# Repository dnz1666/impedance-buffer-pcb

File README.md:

# Impedance Buffer – PCB Design (RWTH Aachen)

Analog circuit design for a student electric vehicle project (elective module, RWTH Aachen University).

## Circuit Design

- Impedance buffer with low-pass filter
- Non-inverting OpAmp amplifier
- Single-sided PCB layout

## Tools

- KiCad (Schematic + PCB Layout)
- PCB fabrication via university lab

## Status

- [x] Schematic
- [x] PCB Layout
- [x] Fabrication & Soldering
- [ ] Microcontroller integration (Arduino)
- [ ] Commissioning & measurement data acquisition

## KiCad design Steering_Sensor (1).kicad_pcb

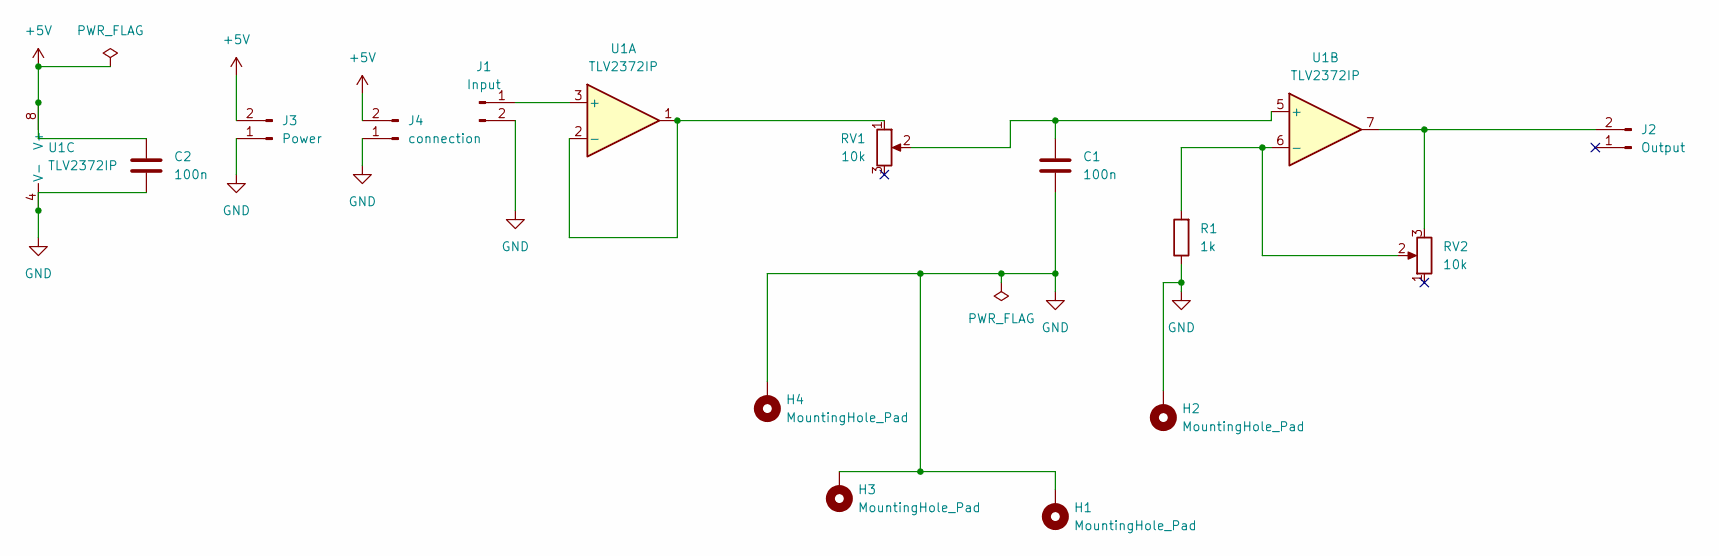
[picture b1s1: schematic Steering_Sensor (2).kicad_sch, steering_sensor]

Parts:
C1, C2: 100n; C_Disc_D5.0mm_W2.5mm_P5.00mm; MPN RDER71H104K0M1H03A
H1, H2, H3, H4: MountingHole_Pad; MountingHole_2.2mm_M2_DIN965_Pad
J1: Input; PinHeader_1x02_P2.54mm_Vertical; MPN 613040167028
J2: Output; PinHeader_1x02_P2.54mm_Vertical; MPN 613040167028
J3: Power; PinHeader_1x02_P2.54mm_Vertical; MPN 613040167028
J4: connection; PinHeader_1x02_P2.54mm_Vertical; MPN 613040167028
R1: 1k; R_Axial_DIN0204_L3.6mm_D1.6mm_P5.08mm_Horizontal
RV1, RV2: 10k; Potentiometer_ACP_CA6-H2,5_Horizontal; MPN CA6XV5-10KA2020SNP
U1: TLV2372IP; DIP-8_W7.62mm_Socket; MPN TLV2372IP

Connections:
+5V: C2.1, J3.2, J4.2, U1.8 (V+)
GND: C1.2, C2.2, H1.1, H2.1, H3.1, H4.1, J1.2, J3.1, J4.1, R1.1, U1.4 (V-)
unnamed: J1.1, U1.3 (+)
unnamed: J2.2, RV2.3, U1.7
unnamed: RV1.1, U1.1, U1.2 (-)
unnamed: C1.1, RV1.2, U1.5 (+)
unnamed: R1.2, RV2.2, U1.6 (-)

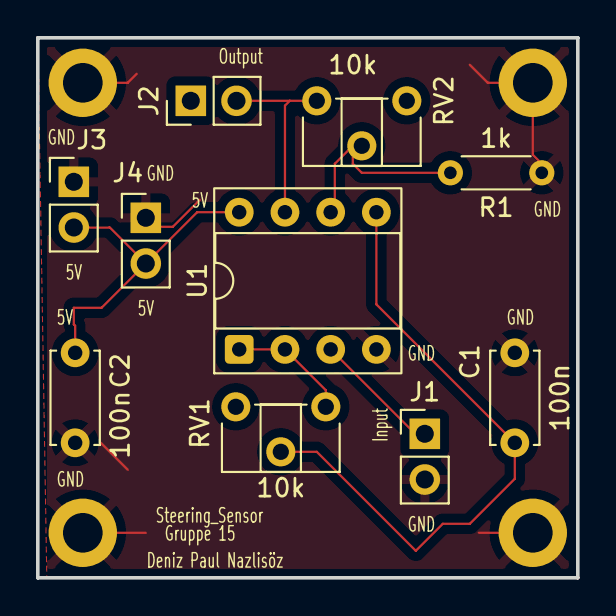
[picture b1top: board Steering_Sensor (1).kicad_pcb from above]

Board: 2 copper layers, 30.0 x 30.0 mm, 14 parts (0 on the bottom side), 7 nets.
